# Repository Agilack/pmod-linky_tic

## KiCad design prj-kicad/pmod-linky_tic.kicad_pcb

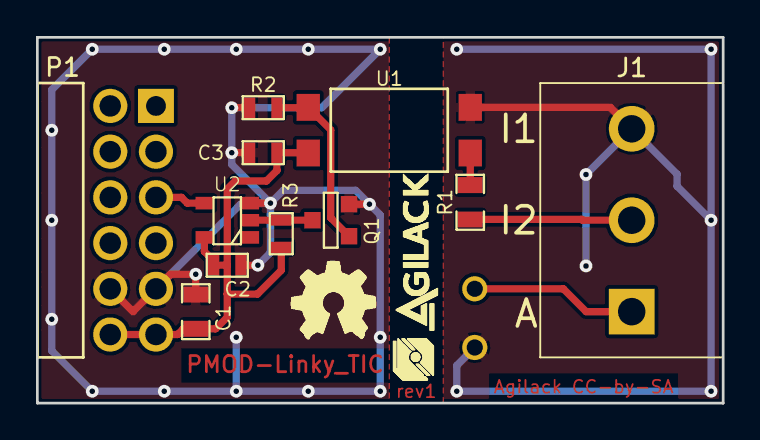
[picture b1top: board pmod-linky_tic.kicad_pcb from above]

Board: 2 copper layers, 38.1 x 20.3 mm, 15 parts (0 on the bottom side), 9 nets.

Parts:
C1: 10uF; SMD0805
C2, C3: 100nF; SMD0603
J1: CONN_3; CONN_MC000035
P1: PMOD; CONN_PMOD-Male
Q1: SI2318; SOT23-3
R1: 4,7k; SMD0805
R2, R3: 10k; SMD0603
TP1, TP2: CONN_1; TP_PIN
U1: LTV814; SMD4
U2: SN74LVC1G17; SOT23-5
agilack-11.5: 450px; logo-agilack-11.5
ohw_logo: VAL**; logo-ohw

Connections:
/TIC_A: J1.1, TP1.1
/TIC_I2: J1.2, R1.1
GND: C1.2, C2.2, C3.2, P1.5, P1.11, Q1.2, R2.2, U2.3
GNDGRID: J1.3, TP2.1, U1.2
unnamed: Q1.1, R2.1, U1.3
unnamed: Q1.3, R3.2, U2.2
unnamed: R1.2, U1.1
PMOD_RXD: P1.3, U2.4
VCC: C1.1, C2.1, C3.1, P1.6, P1.12, R3.1, U1.4, U2.5

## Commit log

2020-09-01 --=={ Initial version }==-- ADD schematics, routing and production files

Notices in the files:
prj-kicad/pmod-linky_tic.kicad_pcb:
License: CC-by-SA 2.0
Agilack CC-by-SA
